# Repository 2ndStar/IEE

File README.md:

This is a PCB project for a 60% + XT column keyboard. It has a very specific fixed layout
1. Fixed split backspace
2. Fixed bottom row: 1.5u 1.25u 1.5u 2.75u 2.25u 1.5u 1.5u 1.25u 1.5u

There is a small issue with the "KC_Grave" key located at Row1 Column8.
Take a look at the schematic and fix it for yourself.

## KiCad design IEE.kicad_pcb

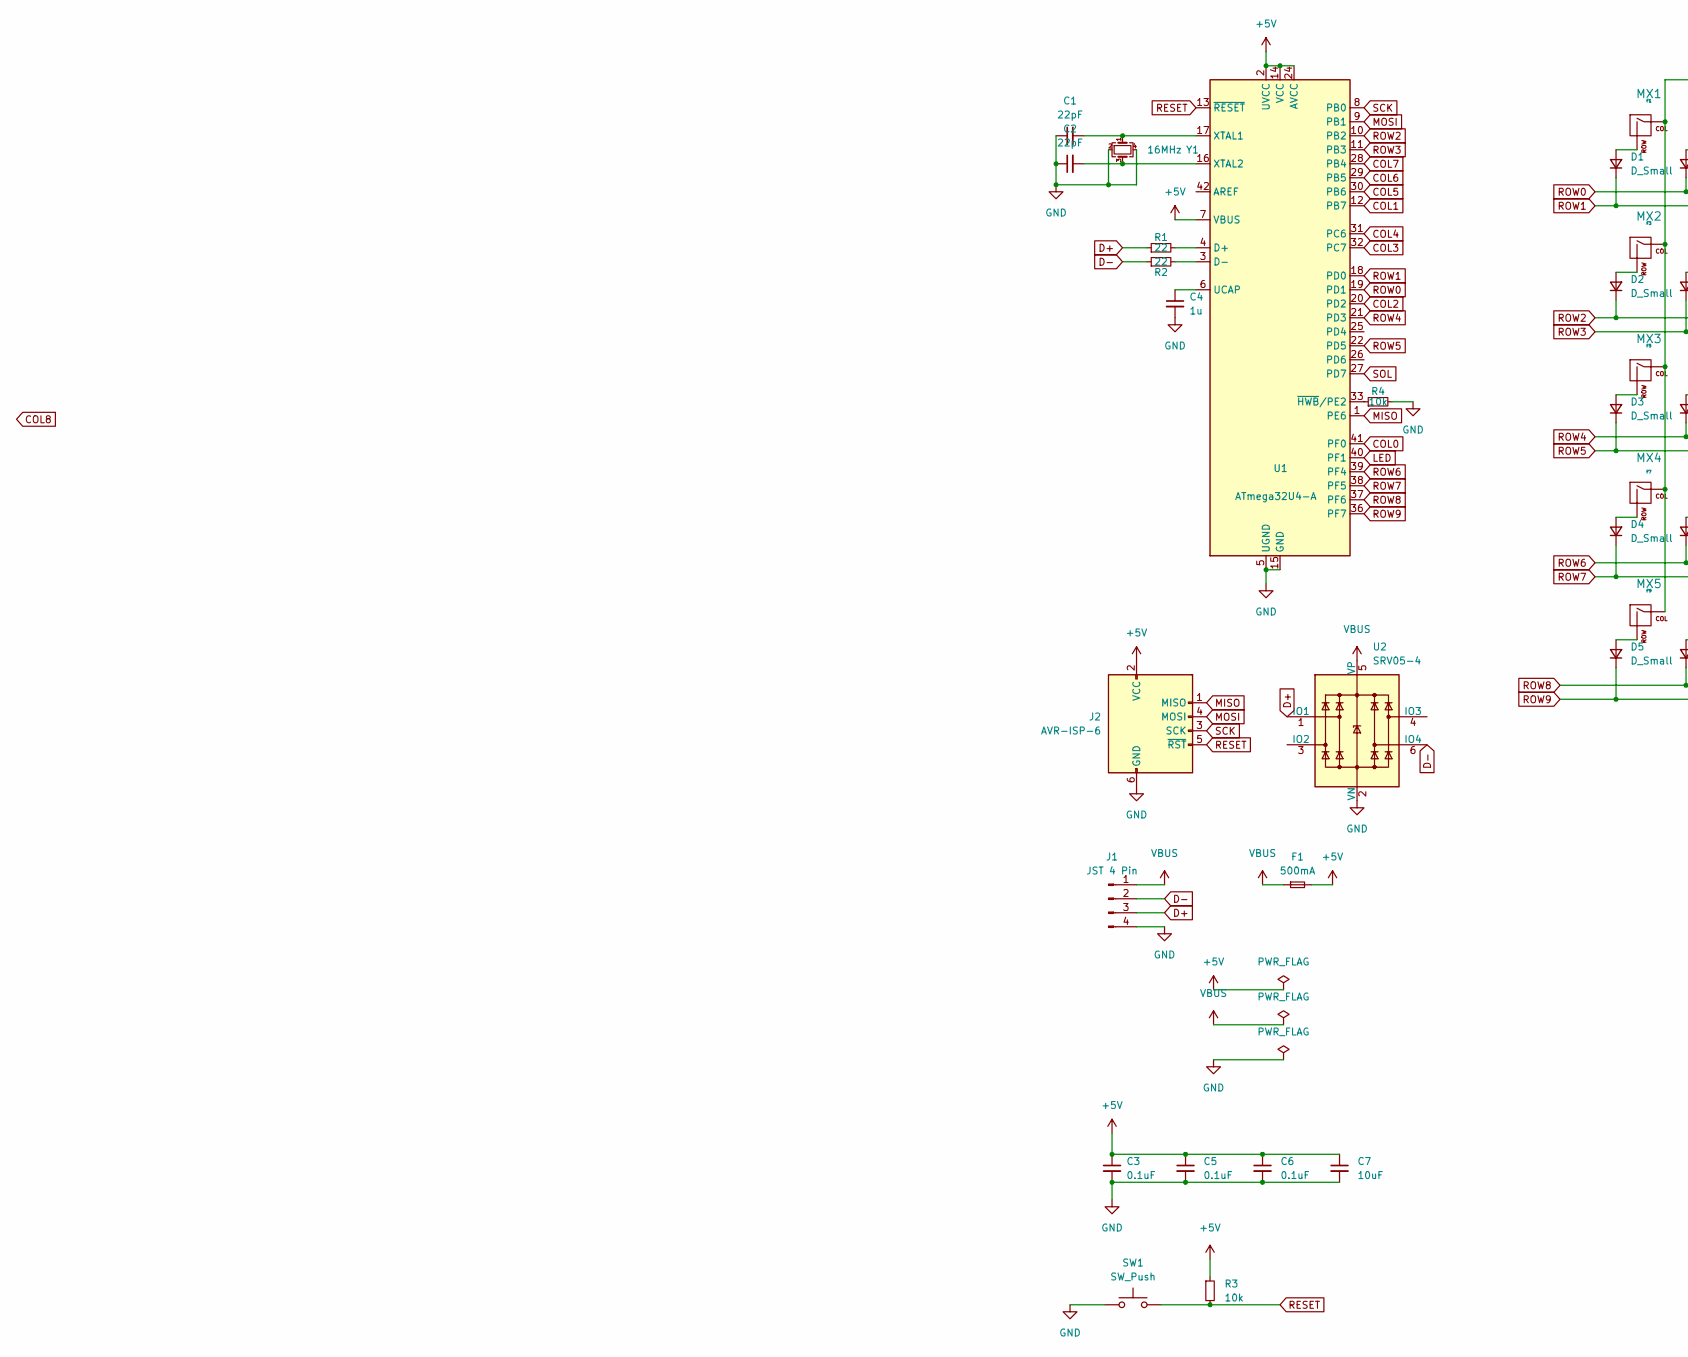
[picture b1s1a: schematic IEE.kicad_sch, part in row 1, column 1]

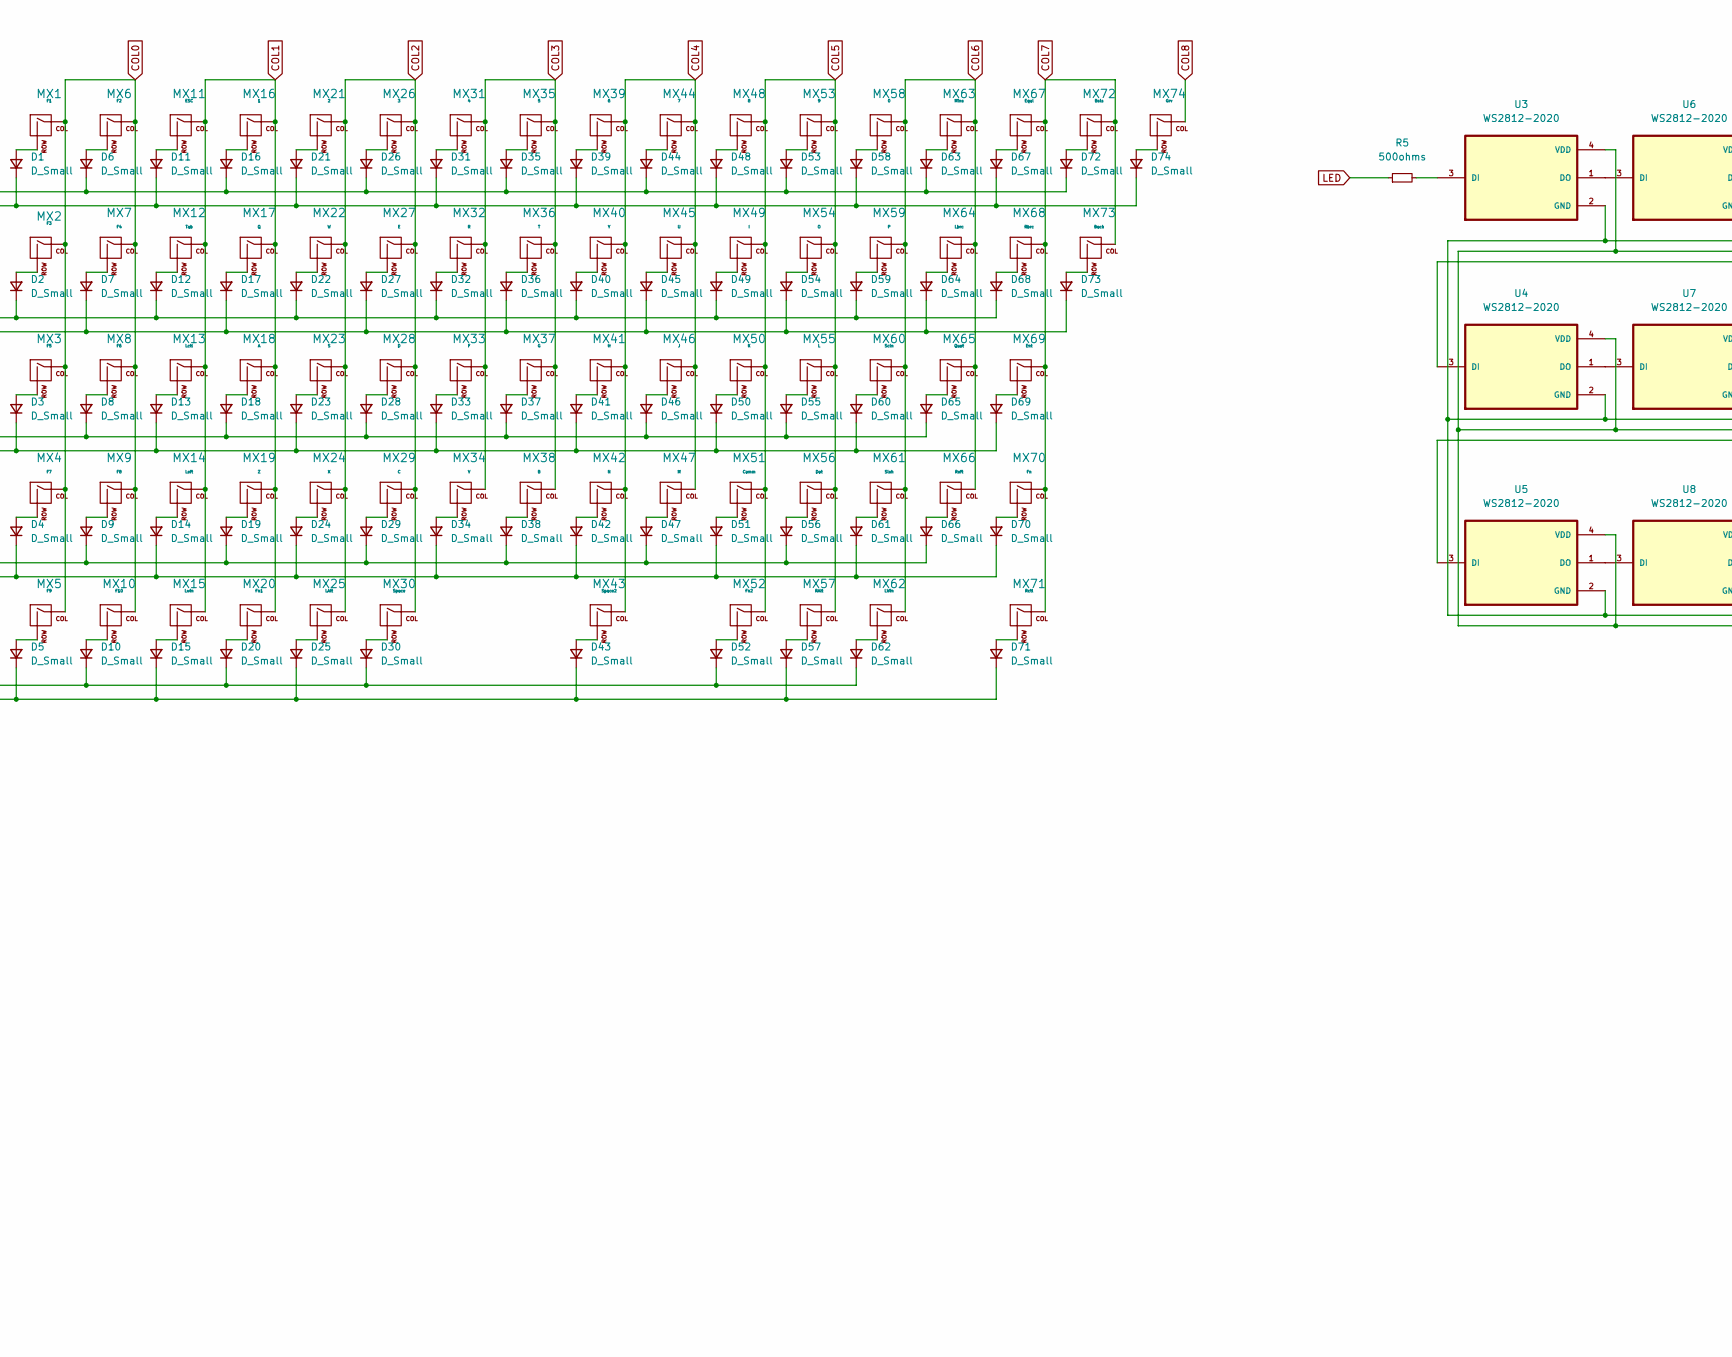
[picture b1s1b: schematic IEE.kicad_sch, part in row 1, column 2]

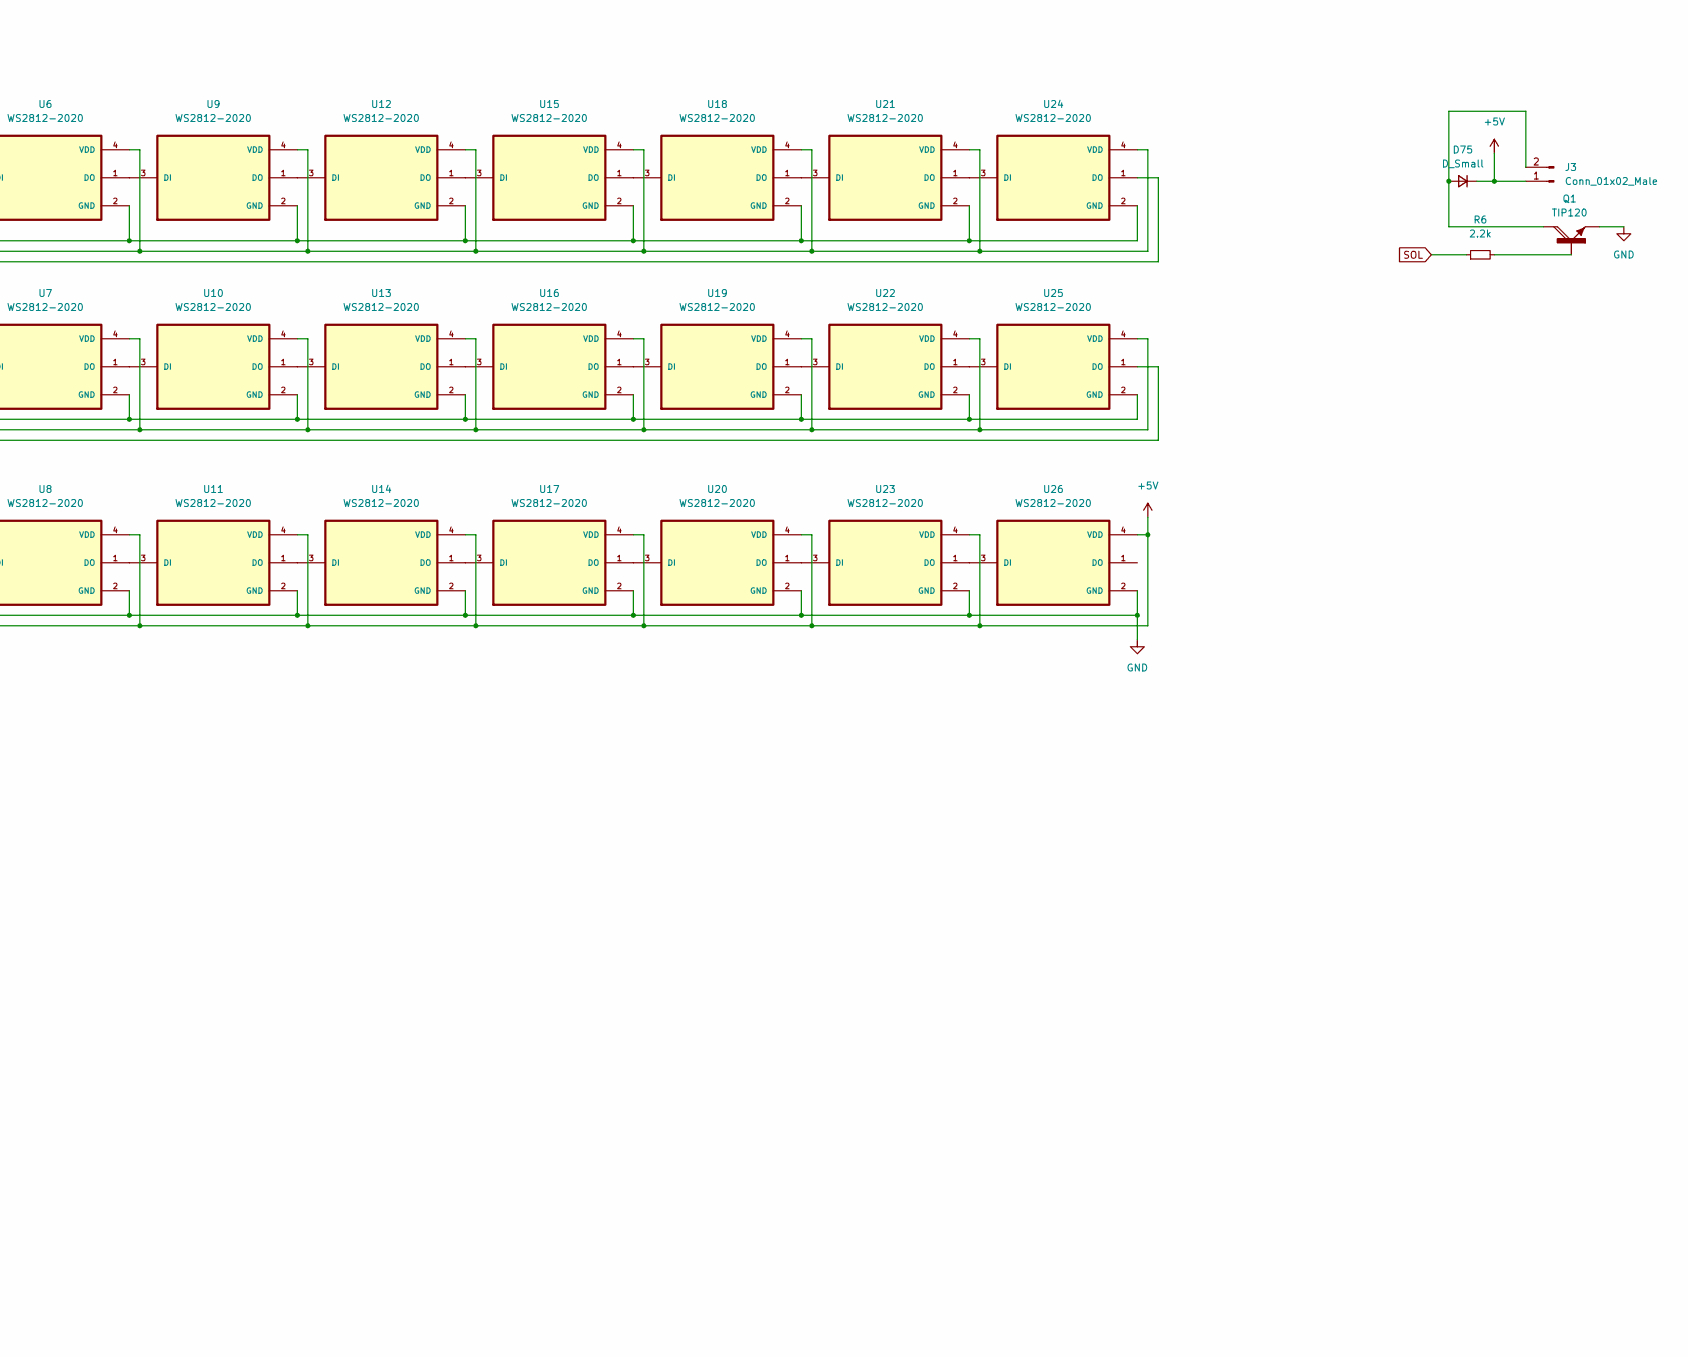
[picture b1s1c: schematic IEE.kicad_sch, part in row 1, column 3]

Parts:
C1, C2: 22pF; C_0805_2012Metric
C3, C5, C6: 0.1uF; C_0805_2012Metric
C4: 1u; C_0805_2012Metric
C7: 10uF; C_0805_2012Metric
D1, D2, D3, D4, D5, D6, D7, D8, D9, D10, D11, D12, D13, D14, D15, D16, D17, D18, D19, D20, D21, D22, D23, D24, D25, D26, D27, D28, D29, D30, D31, D32, D33, D34, D35, D36, D37, D38, D39, D40, D41, D42, D43, D44, D45, D46, D47, D48, D49, D50, D51, D52, D53, D54, D55, D56, D57, D58, D59, D60, D61, D62, D63, D64, D65, D66, D67, D68, D69, D70, D71, D72, D73, D74: D_Small; D_SOD-123
D75: D_Small; D_SOD-123F
F1: 500mA; Fuse_1206_3216Metric
J1: JST 4 Pin; JST-SR-4
J2: AVR-ISP-6; ISP
J3: Conn_01x02_Male; JST_S2B-PH-K-S(LF)(SN)
MX1: F1; MXOnly-1U-NoLED
MX2: F3; MXOnly-1U-NoLED
MX3: F5; MXOnly-1U-NoLED
MX4: F7; MXOnly-1U-NoLED
MX5: F9; MXOnly-1U-NoLED
MX6: F2; MXOnly-1U-NoLED
MX7: F4; MXOnly-1U-NoLED
MX8: F6; MXOnly-1U-NoLED
MX9: F8; MXOnly-1U-NoLED
MX10: F10; MXOnly-1U-NoLED
MX11: ESC; MXOnly-1U-NoLED
MX12: Tab; MXOnly-1.5U-NoLED
MX13: Lctl; MXOnly-1.75U-NoLED
MX14: Lsft; MXOnly-2.25U-NoLED
MX15: Lwin; MXOnly-1.5U-NoLED
MX16: 1; MXOnly-1U-NoLED
MX17: Q; MXOnly-1U-NoLED
MX18: A; MXOnly-1U-NoLED
MX19: Z; MXOnly-1U-NoLED
MX20: Fn1; MXOnly-1.25U-NoLED
MX21: 2; MXOnly-1U-NoLED
MX22: W; MXOnly-1U-NoLED
MX23: S; MXOnly-1U-NoLED
MX24: X; MXOnly-1U-NoLED
MX25: LAlt; MXOnly-1.5U-NoLED
MX26: 3; MXOnly-1U-NoLED
MX27: E; MXOnly-1U-NoLED
MX28: D; MXOnly-1U-NoLED
MX29: C; MXOnly-1U-NoLED
MX30: Space; MXOnly-2.75U-ReversedStabilizers-NoLED
MX31: 4; MXOnly-1U-NoLED
MX32: R; MXOnly-1U-NoLED
MX33: F; MXOnly-1U-NoLED
MX34: V; MXOnly-1U-NoLED
MX35: 5; MXOnly-1U-NoLED
MX36: T; MXOnly-1U-NoLED
MX37: G; MXOnly-1U-NoLED
MX38: B; MXOnly-1U-NoLED
MX39: 6; MXOnly-1U-NoLED
MX40: Y; MXOnly-1U-NoLED
MX41: H; MXOnly-1U-NoLED
MX42: N; MXOnly-1U-NoLED
MX43: Space2; MXOnly-2.25U-ReversedStabilizers-NoLED
MX44: 7; MXOnly-1U-NoLED
MX45: U; MXOnly-1U-NoLED
MX46: J; MXOnly-1U-NoLED
MX47: M; MXOnly-1U-NoLED
MX48: 8; MXOnly-1U-NoLED
MX49: I; MXOnly-1U-NoLED
MX50: K; MXOnly-1U-NoLED
MX51: Comm; MXOnly-1U-NoLED
MX52: Fn2; MXOnly-1.5U-NoLED
MX53: 9; MXOnly-1U-NoLED
MX54: O; MXOnly-1U-NoLED
MX55: L; MXOnly-1U-NoLED
MX56: Dot; MXOnly-1U-NoLED
MX57: RAlt; MXOnly-1.5U-NoLED
MX58: 0; MXOnly-1U-NoLED
MX59: P; MXOnly-1U-NoLED
MX60: Scln; MXOnly-1U-NoLED
MX61: Slsh; MXOnly-1U-NoLED
MX62: LWin; MXOnly-1.25U-NoLED
MX63: Mins; MXOnly-1U-NoLED
MX64: Lbrc; MXOnly-1U-NoLED
MX65: Quot; MXOnly-1U-NoLED
MX66: Rsft; MXOnly-1.75U-NoLED
MX67: Equl; MXOnly-1U-NoLED
MX68: Rbrc; MXOnly-1U-NoLED
MX69: Ent; MXOnly-2.25U-NoLED
MX70: Fn; MXOnly-1U-NoLED
MX71: Rctl; MXOnly-1.5U-NoLED
MX72: Bsls; MXOnly-1U-NoLED
MX73: Back; MXOnly-1.5U-NoLED
MX74: Grv; MXOnly-1U-NoLED
Q1: TIP120; TO220AH
R1, R2: 22; R_0805_2012Metric
R3, R4: 10k; R_0805_2012Metric
R5: 500ohms; R_0805_2012Metric
R6: 2.2k; R_0805_2012Metric
SW1: SW_Push; SKQG-1155865
U1: ATmega32U4-A; TQFP-44_10x10mm_P0.8mm
U2: SRV05-4; SOT-23-6
U3, U4, U5, U6, U7, U8, U9, U10, U11, U12, U13, U14, U15, U16, U17, U18, U19, U20, U21, U22, U23, U24, U25, U26: WS2812-2020; LED_WS2812-2020
Y1: 16MHz; Crystal_SMD_3225-4Pin_3.2x2.5mm

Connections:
+5V: C3.1, C5.1, C6.1, C7.1, D75.1 (K), F1.2, J2.2 (VCC), J3.1, R3.1, U1.2 (UVCC), U1.7 (VBUS), U1.14 (VCC), U1.24 (AVCC), U1.34 (VCC), U1.44 (AVCC), U3.4 (VDD), U4.4 (VDD), U5.4 (VDD), U6.4 (VDD), U7.4 (VDD), U8.4 (VDD), U9.4 (VDD), U10.4 (VDD), U11.4 (VDD), U12.4 (VDD), U13.4 (VDD), U14.4 (VDD), U15.4 (VDD), U16.4 (VDD), U17.4 (VDD), U18.4 (VDD), U19.4 (VDD), U20.4 (VDD), U21.4 (VDD), U22.4 (VDD), U23.4 (VDD), U24.4 (VDD), U25.4 (VDD), U26.4 (VDD)
COL0: MX1.1 (COL), MX2.1 (COL), MX3.1 (COL), MX4.1 (COL), MX5.1 (COL), MX6.1 (COL), MX7.1 (COL), MX8.1 (COL), MX9.1 (COL), MX10.1 (COL), U1.41 (PF0)
COL1: MX11.1 (COL), MX12.1 (COL), MX13.1 (COL), MX14.1 (COL), MX15.1 (COL), MX16.1 (COL), MX17.1 (COL), MX18.1 (COL), MX19.1 (COL), MX20.1 (COL), U1.12 (PB7)
COL2: MX21.1 (COL), MX22.1 (COL), MX23.1 (COL), MX24.1 (COL), MX25.1 (COL), MX26.1 (COL), MX27.1 (COL), MX28.1 (COL), MX29.1 (COL), MX30.1 (COL), U1.20 (PD2)
COL3: MX31.1 (COL), MX32.1 (COL), MX33.1 (COL), MX34.1 (COL), MX35.1 (COL), MX36.1 (COL), MX37.1 (COL), MX38.1 (COL), U1.32 (PC7)
COL4: MX39.1 (COL), MX40.1 (COL), MX41.1 (COL), MX42.1 (COL), MX43.1 (COL), MX44.1 (COL), MX45.1 (COL), MX46.1 (COL), MX47.1 (COL), U1.31 (PC6)
COL5: MX48.1 (COL), MX49.1 (COL), MX50.1 (COL), MX51.1 (COL), MX52.1 (COL), MX53.1 (COL), MX54.1 (COL), MX55.1 (COL), MX56.1 (COL), MX57.1 (COL), U1.30 (PB6)
COL6: MX58.1 (COL), MX59.1 (COL), MX60.1 (COL), MX61.1 (COL), MX62.1 (COL), MX63.1 (COL), MX64.1 (COL), MX65.1 (COL), MX66.1 (COL), U1.29 (PB5)
COL7: MX67.1 (COL), MX68.1 (COL), MX69.1 (COL), MX70.1 (COL), MX71.1 (COL), MX72.1 (COL), MX73.1 (COL), U1.28 (PB4)
COL8: MX74.1 (COL)
D+: J1.3, R1.1, U2.1 (IO1)
D-: J1.2, R2.1, U2.6 (IO4)
GND: C1.1, C2.1, C3.2, C4.2, C5.2, C6.2, C7.2, J1.4, J2.6 (GND), Q1.E, R4.2, SW1.1, U1.5 (UGND), U1.15 (GND), U1.23 (GND), U1.35 (GND), U1.43 (GND), U2.2 (VN), U3.2 (GND), U4.2 (GND), U5.2 (GND), U6.2 (GND), U7.2 (GND), U8.2 (GND), U9.2 (GND), U10.2 (GND), U11.2 (GND), U12.2 (GND), U13.2 (GND), U14.2 (GND), U15.2 (GND), U16.2 (GND), U17.2 (GND), U18.2 (GND), U19.2 (GND), U20.2 (GND), U21.2 (GND), U22.2 (GND), U23.2 (GND), U24.2 (GND), U25.2 (GND), U26.2 (GND), Y1.2, Y1.4
LED: R5.1, U1.40 (PF1)
MISO: J2.1 (MISO), U1.1 (PE6)
MOSI: J2.4 (MOSI), U1.9 (PB1)
unnamed: C1.2, U1.17 (XTAL1), Y1.1
unnamed: C2.2, U1.16 (XTAL2), Y1.3
unnamed: C4.1, U1.6 (UCAP)
unnamed: D1.2 (A), MX1.2 (ROW)
unnamed: D2.2 (A), MX2.2 (ROW)
unnamed: D3.2 (A), MX3.2 (ROW)
unnamed: D4.2 (A), MX4.2 (ROW)
unnamed: D5.2 (A), MX5.2 (ROW)
unnamed: D6.2 (A), MX6.2 (ROW)
unnamed: D7.2 (A), MX7.2 (ROW)
unnamed: D8.2 (A), MX8.2 (ROW)
unnamed: D9.2 (A), MX9.2 (ROW)
unnamed: D10.2 (A), MX10.2 (ROW)
unnamed: D11.2 (A), MX11.2 (ROW)
unnamed: D12.2 (A), MX12.2 (ROW)
unnamed: D13.2 (A), MX13.2 (ROW)
unnamed: D14.2 (A), MX14.2 (ROW)
unnamed: D15.2 (A), MX15.2 (ROW)
unnamed: D16.2 (A), MX16.2 (ROW)
unnamed: D17.2 (A), MX17.2 (ROW)
unnamed: D18.2 (A), MX18.2 (ROW)
unnamed: D19.2 (A), MX19.2 (ROW)
unnamed: D20.2 (A), MX20.2 (ROW)
unnamed: D21.2 (A), MX21.2 (ROW)
unnamed: D22.2 (A), MX22.2 (ROW)
unnamed: D23.2 (A), MX23.2 (ROW)
unnamed: D24.2 (A), MX24.2 (ROW)
unnamed: D25.2 (A), MX25.2 (ROW)
unnamed: D26.2 (A), MX26.2 (ROW)
unnamed: D27.2 (A), MX27.2 (ROW)
unnamed: D28.2 (A), MX28.2 (ROW)
unnamed: D29.2 (A), MX29.2 (ROW)
unnamed: D30.2 (A), MX30.2 (ROW)
unnamed: D31.2 (A), MX31.2 (ROW)
unnamed: D32.2 (A), MX32.2 (ROW)
unnamed: D33.2 (A), MX33.2 (ROW)
unnamed: D34.2 (A), MX34.2 (ROW)
unnamed: D35.2 (A), MX35.2 (ROW)
unnamed: D36.2 (A), MX36.2 (ROW)
unnamed: D37.2 (A), MX37.2 (ROW)
unnamed: D38.2 (A), MX38.2 (ROW)
unnamed: D39.2 (A), MX39.2 (ROW)
unnamed: D40.2 (A), MX40.2 (ROW)
unnamed: D41.2 (A), MX41.2 (ROW)
unnamed: D42.2 (A), MX42.2 (ROW)
unnamed: D43.2 (A), MX43.2 (ROW)
unnamed: D44.2 (A), MX44.2 (ROW)
unnamed: D45.2 (A), MX45.2 (ROW)
unnamed: D46.2 (A), MX46.2 (ROW)
unnamed: D47.2 (A), MX47.2 (ROW)
unnamed: D48.2 (A), MX48.2 (ROW)
unnamed: D49.2 (A), MX49.2 (ROW)
unnamed: D50.2 (A), MX50.2 (ROW)
unnamed: D51.2 (A), MX51.2 (ROW)
unnamed: D52.2 (A), MX52.2 (ROW)
unnamed: D53.2 (A), MX53.2 (ROW)
unnamed: D54.2 (A), MX54.2 (ROW)
unnamed: D55.2 (A), MX55.2 (ROW)
unnamed: D56.2 (A), MX56.2 (ROW)
unnamed: D57.2 (A), MX57.2 (ROW)
unnamed: D58.2 (A), MX58.2 (ROW)
unnamed: D59.2 (A), MX59.2 (ROW)
unnamed: D60.2 (A), MX60.2 (ROW)
unnamed: D61.2 (A), MX61.2 (ROW)
unnamed: D62.2 (A), MX62.2 (ROW)
unnamed: D63.2 (A), MX63.2 (ROW)
unnamed: D64.2 (A), MX64.2 (ROW)
unnamed: D65.2 (A), MX65.2 (ROW)
unnamed: D66.2 (A), MX66.2 (ROW)
unnamed: D67.2 (A), MX67.2 (ROW)
unnamed: D68.2 (A), MX68.2 (ROW)
unnamed: D69.2 (A), MX69.2 (ROW)
unnamed: D70.2 (A), MX70.2 (ROW)
unnamed: D71.2 (A), MX71.2 (ROW)
unnamed: D72.2 (A), MX72.2 (ROW)
unnamed: D73.2 (A), MX73.2 (ROW)
unnamed: D74.2 (A), MX74.2 (ROW)
unnamed: D75.2 (A), J3.2, Q1.C
unnamed: Q1.B, R6.2
unnamed: R1.2, U1.4 (D+)
unnamed: R2.2, U1.3 (D-)
unnamed: R4.1, U1.33 (~HWB/PE2)
unnamed: R5.2, U3.3 (DI)
unnamed: U3.1 (DO), U6.3 (DI)
unnamed: U4.1 (DO), U7.3 (DI)
unnamed: U5.1 (DO), U8.3 (DI)
unnamed: U6.1 (DO), U9.3 (DI)
unnamed: U10.1 (DO), U13.3 (DI)
unnamed: U7.1 (DO), U10.3 (DI)
unnamed: U11.1 (DO), U14.3 (DI)
unnamed: U8.1 (DO), U11.3 (DI)
unnamed: U12.1 (DO), U15.3 (DI)
unnamed: U9.1 (DO), U12.3 (DI)
unnamed: U13.1 (DO), U16.3 (DI)
unnamed: U14.1 (DO), U17.3 (DI)
unnamed: U15.1 (DO), U18.3 (DI)
unnamed: U16.1 (DO), U19.3 (DI)
unnamed: U17.1 (DO), U20.3 (DI)
unnamed: U18.1 (DO), U21.3 (DI)
unnamed: U19.1 (DO), U22.3 (DI)
unnamed: U20.1 (DO), U23.3 (DI)
unnamed: U21.1 (DO), U24.3 (DI)
unnamed: U22.1 (DO), U25.3 (DI)
unnamed: U23.1 (DO), U26.3 (DI)
unnamed: U4.3 (DI), U24.1 (DO)
unnamed: U5.3 (DI), U25.1 (DO)
RESET: J2.5 (~RST), R3.2, SW1.2, U1.13 (~RESET)
ROW0: D6.1 (K), D16.1 (K), D26.1 (K), D35.1 (K), D44.1 (K), D53.1 (K), D63.1 (K), D72.1 (K), U1.19 (PD1)
ROW1: D1.1 (K), D11.1 (K), D21.1 (K), D31.1 (K), D39.1 (K), D48.1 (K), D58.1 (K), D67.1 (K), D74.1 (K), U1.18 (PD0)
ROW2: D2.1 (K), D12.1 (K), D22.1 (K), D32.1 (K), D40.1 (K), D49.1 (K), D59.1 (K), D68.1 (K), U1.10 (PB2)
ROW3: D7.1 (K), D17.1 (K), D27.1 (K), D36.1 (K), D45.1 (K), D54.1 (K), D64.1 (K), D73.1 (K), U1.11 (PB3)
ROW4: D8.1 (K), D18.1 (K), D28.1 (K), D37.1 (K), D46.1 (K), D55.1 (K), D65.1 (K), U1.21 (PD3)
ROW5: D3.1 (K), D13.1 (K), D23.1 (K), D33.1 (K), D41.1 (K), D50.1 (K), D60.1 (K), D69.1 (K), U1.22 (PD5)
ROW6: D9.1 (K), D19.1 (K), D29.1 (K), D38.1 (K), D47.1 (K), D56.1 (K), D66.1 (K), U1.39 (PF4)
ROW7: D4.1 (K), D14.1 (K), D24.1 (K), D34.1 (K), D42.1 (K), D51.1 (K), D61.1 (K), D70.1 (K), U1.38 (PF5)
ROW8: D10.1 (K), D20.1 (K), D30.1 (K), D52.1 (K), D62.1 (K), U1.37 (PF6)
ROW9: D5.1 (K), D15.1 (K), D25.1 (K), D43.1 (K), D57.1 (K), D71.1 (K), U1.36 (PF7)
SCK: J2.3 (SCK), U1.8 (PB0)
SOL: R6.1, U1.27 (PD7)
VBUS: F1.1, J1.1, U2.5 (VP)

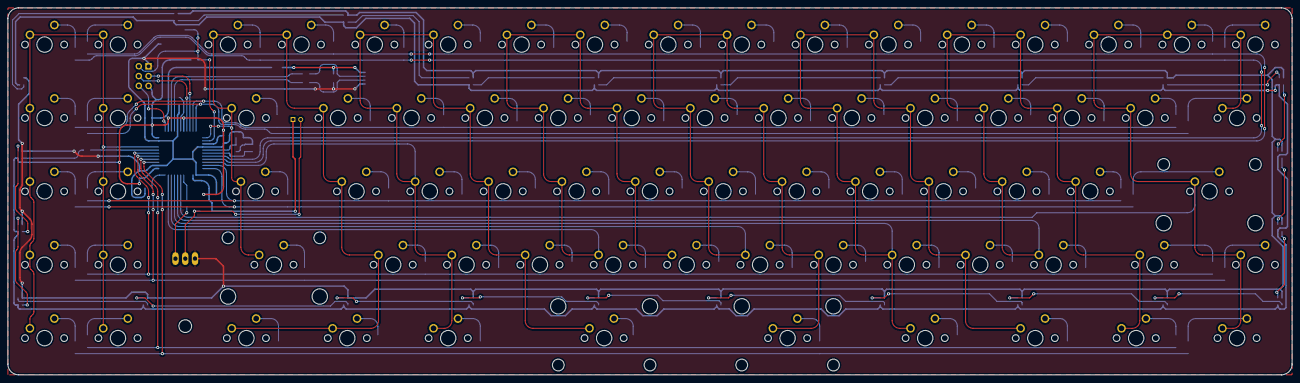
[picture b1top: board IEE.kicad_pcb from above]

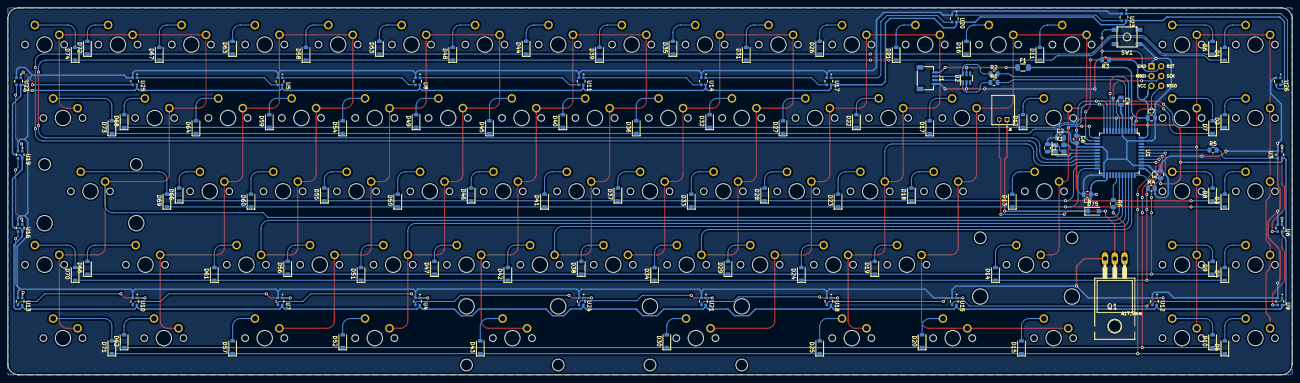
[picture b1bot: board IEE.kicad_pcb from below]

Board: 2 copper layers, 333.4 x 95.2 mm, 195 parts (121 on the bottom side), 135 nets.

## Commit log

2022-08-14 Initial commit of already made PCB
2022-08-15 Add Firmware VIAL and QMK in IEE-Firmware folder
2022-08-15 Modified README
